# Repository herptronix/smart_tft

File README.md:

Smart TFT module
================

Open source (hardware & software) smart TFT module, based on:
 - Microchip PIC32MX795F512L microcontroller
 - 3.2" TFT 320x240, ILI9320/9325 controller
 - optional µSD card, for extra storage

This module has three operational modes:
 - slave: an other microcontroller sends commands to the TFT through UART (1M bauds, 8N1)
 - embedded app: the user includes its application directly into the PIC32
 - setup: setup menu, for touchscreen callibration, gamma adjustement & software demo; enter this mode by keeping the touchscreen pressed while powering on the 5V PSU.

Small video: https://www.youtube.com/watch?v=Nt97tPhJtdA
Some explanations (french only): http://herptronix.blogspot.fr/

## Pins & wirepads description ##

## Software modules ##

## Screenshots ##

## Pickit3 ##

Status
======

Maintained

 - 2014/03/31 Add sprite & font converters (sources & win32 exe)
 - 2014/02/27 Add display orientation support (limited to BSP) & Minor bug fixes
 - 2014/02/01 Minor bug fixes (p2d_font.c / touchCalib.c / gui_w_usr_entry.c)
 - 2014/01/15 Add a quick & dirty (... and not yet completed) dev. guide
 - 2014/01/09 Add a serial remote example
 - 2013/12/29 Rev. A (improved P2D/GUI, FAT-FS support, setup menu, serial comm support)
 - 2013/08/11 First GUI version (not on git)
 - 2013/07/13 First P2D version (not on git)

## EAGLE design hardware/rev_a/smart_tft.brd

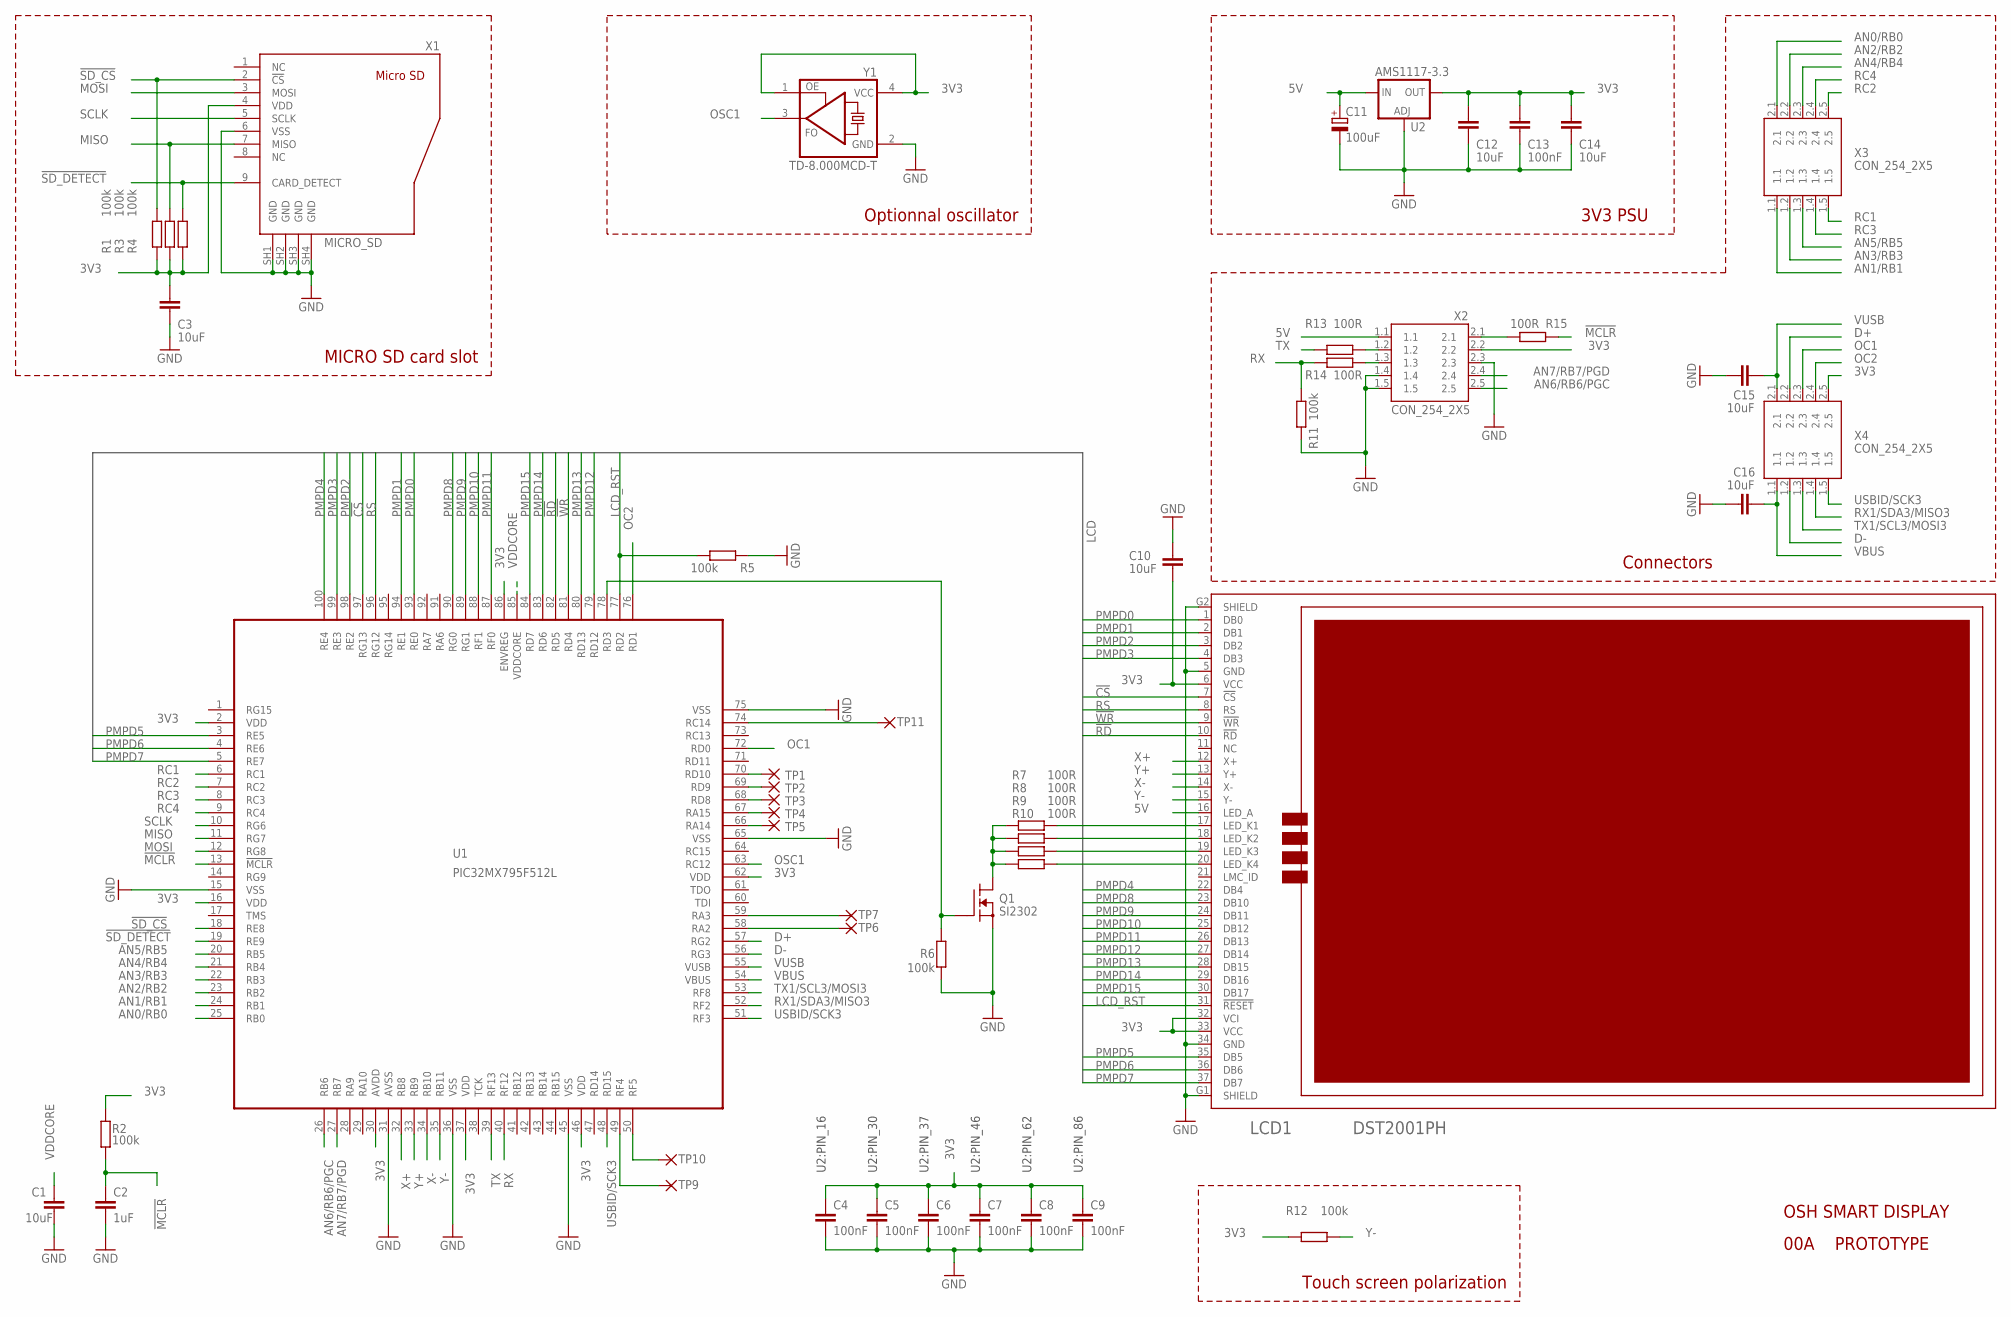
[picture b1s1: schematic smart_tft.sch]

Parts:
C1, C3, C10, C12, C14, C15, C16: 10uF; C0805
C2: 1uF; C0603
C4, C5, C6, C7, C8, C9, C13: 100nF; C0603
C11: 100uF; SMC_D
LCD1: DST2001PH
Q1: SI2302; SOT23-BEC
R1, R2, R3, R4, R5, R6, R11, R12: 100k; R0603
R7, R8, R9, R10, R13, R14, R15: 100R; R0603
TP1, TP2, TP3, TP4, TP5, TP6, TP7, TP9, TP10, TP11: 1.27R
U1: PIC32MX795F512L; TQFP100-14X14
U2: AMS1117-3.3; SOT223
X1: MICRO_SD; SD_MICRO
X2, X3, X4: CON_254_2X5; 2X5_CMS
Y1: TD-8.000MCD-T; ASF

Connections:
3V3: C3.1, C4.1, C5.1, C6.1, C7.1, C8.1, C9.1, C10.2, C12.1, C13.1, C14.1, LCD1.6 (VCC), LCD1.32 (VCI), LCD1.33 (VCC), R1.1, R2.2, R3.2, R4.2, R12.2, U1.2 (VDD), U1.16 (VDD), U1.30 (AVDD), U1.37 (VDD), U1.46 (VDD), U1.62 (VDD), U1.86 (ENVREG), U2.4 (OUT), X1.4 (VDD), X2.2.2, X4.2.5, Y1.1 (OE), Y1.4 (VCC)
5V: C11.+, LCD1.16 (LED_A), U2.3 (IN), X2.1.1
!CS: LCD1.7 (!CS), U1.97 (RG13)
!MCLR: C2.1, R2.1, R15.1, U1.13 (!MCLR)
!RD: LCD1.10 (!RD), U1.82 (RD5)
!SD_CS: R1.2, U1.18 (RE8), X1.2 (!CS)
!SD_DETECT: R4.1, U1.19 (RE9), X1.9 (CARD_DETECT)
!WR: LCD1.9 (!WR), U1.81 (RD4)
AN0/RB0: U1.25 (RB0), X3.2.1
AN1/RB1: U1.24 (RB1), X3.1.1
AN2/RB2: U1.23 (RB2), X3.2.2
AN3/RB3: U1.22 (RB3), X3.1.2
AN4/RB4: U1.21 (RB4), X3.2.3
AN5/RB5: U1.20 (RB5), X3.1.3
AN6/RB6/PGC: U1.26 (RB6), X2.2.5
AN7/RB7/PGD: U1.27 (RB7), X2.2.4
D+: U1.57 (RG2), X4.2.2
D-: U1.56 (RG3), X4.1.2
GND: C1.1, C2.2, C3.2, C4.2, C5.2, C6.2, C7.2, C8.2, C9.2, C10.1, C11.-, C12.2, C13.2, C14.2, C15.2, C16.2, LCD1.5 (GND), LCD1.34 (GND), LCD1.G1 (SHIELD), LCD1.G2 (SHIELD), Q1.E (S), R5.1, R6.1, R11.1, U1.15 (VSS), U1.31 (AVSS), U1.36 (VSS), U1.45 (VSS), U1.65 (VSS), U1.75 (VSS), U2.1 (ADJ), X1.6 (VSS), X1.SH1 (GND), X1.SH2 (GND), X1.SH3 (GND), X1.SH4 (GND), X2.1.4, X2.1.5, X2.2.3, Y1.2 (GND)
LCD_RST: LCD1.31 (!RESET), R5.2, U1.77 (RD2)
MISO: R3.1, U1.11 (RG7), X1.7 (MISO)
MOSI: U1.12 (RG8), X1.3 (MOSI)
unnamed: TP6.P$1, U1.58 (RA2)
unnamed: Q1.C (D), R7.1, R8.1, R9.1, R10.1
unnamed: Q1.B (G), R6.2, U1.78 (RD3)
unnamed: R13.2, X2.1.2
unnamed: R14.2, X2.1.3
unnamed: TP7.P$1, U1.59 (RA3)
unnamed: TP5.P$1, U1.66 (RA14)
unnamed: TP4.P$1, U1.67 (RA15)
unnamed: LCD1.20 (LED_K4), R10.2
unnamed: LCD1.19 (LED_K3), R9.2
unnamed: LCD1.18 (LED_K2), R8.2
unnamed: LCD1.17 (LED_K1), R7.2
unnamed: TP3.P$1, U1.68 (RD8)
unnamed: TP2.P$1, U1.69 (RD9)
unnamed: TP1.P$1, U1.70 (RD10)
unnamed: TP9.P$1, U1.49 (RF4)
unnamed: TP10.P$1, U1.50 (RF5)
unnamed: TP11.P$1, U1.74 (RC14)
unnamed: R15.2, X2.2.1
OC1: U1.72 (RD0), X4.2.3
OC2: U1.76 (RD1), X4.2.4
OSC1: U1.63 (RC12), Y1.3 (FO)
PMPD0: LCD1.1 (DB0), U1.93 (RE0)
PMPD1: LCD1.2 (DB1), U1.94 (RE1)
PMPD2: LCD1.3 (DB2), U1.98 (RE2)
PMPD3: LCD1.4 (DB3), U1.99 (RE3)
PMPD4: LCD1.22 (DB4), U1.100 (RE4)
PMPD5: LCD1.35 (DB5), U1.3 (RE5)
PMPD6: LCD1.36 (DB6), U1.4 (RE6)
PMPD7: LCD1.37 (DB7), U1.5 (RE7)
PMPD8: LCD1.23 (DB10), U1.90 (RG0)
PMPD9: LCD1.24 (DB11), U1.89 (RG1)
PMPD10: LCD1.25 (DB12), U1.88 (RF1)
PMPD11: LCD1.26 (DB13), U1.87 (RF0)
PMPD12: LCD1.27 (DB14), U1.79 (RD12)
PMPD13: LCD1.28 (DB15), U1.80 (RD13)
PMPD14: LCD1.29 (DB16), U1.83 (RD6)
PMPD15: LCD1.30 (DB17), U1.84 (RD7)
RC1: U1.6 (RC1), X3.1.5
RC2: U1.7 (RC2), X3.2.5
RC3: U1.8 (RC3), X3.1.4
RC4: U1.9 (RC4), X3.2.4
RS: LCD1.8 (RS), U1.96 (RG12)
RX: R11.2, R14.1, U1.40 (RF12)
RX1/SDA3/MISO3: U1.52 (RF2), X4.1.4
SCLK: U1.10 (RG6), X1.5 (SCLK)
TX: R13.1, U1.39 (RF13)
TX1/SCL3/MOSI3: U1.53 (RF8), X4.1.3
USBID/SCK3: U1.48 (RD15), U1.51 (RF3), X4.1.5
VBUS: C16.1, U1.54 (VBUS), X4.1.1
VDDCORE: C1.2, U1.85 (VDDCORE)
VUSB: C15.1, U1.55 (VUSB), X4.2.1
X+: LCD1.12 (X+), U1.32 (RB8)
X-: LCD1.14 (X-), U1.34 (RB10)
Y+: LCD1.13 (Y+), U1.33 (RB9)
Y-: LCD1.15 (Y-), R12.1, U1.35 (RB11)

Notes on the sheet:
PROTOTYPE
00A
U2:PIN_16
U2:PIN_37
U2:PIN_46
U2:PIN_62
U2:PIN_86
U2:PIN_30
Touch screen polarization
MICRO SD card slot
Optionnal oscillator
3V3 PSU
Connectors
OSH SMART DISPLAY

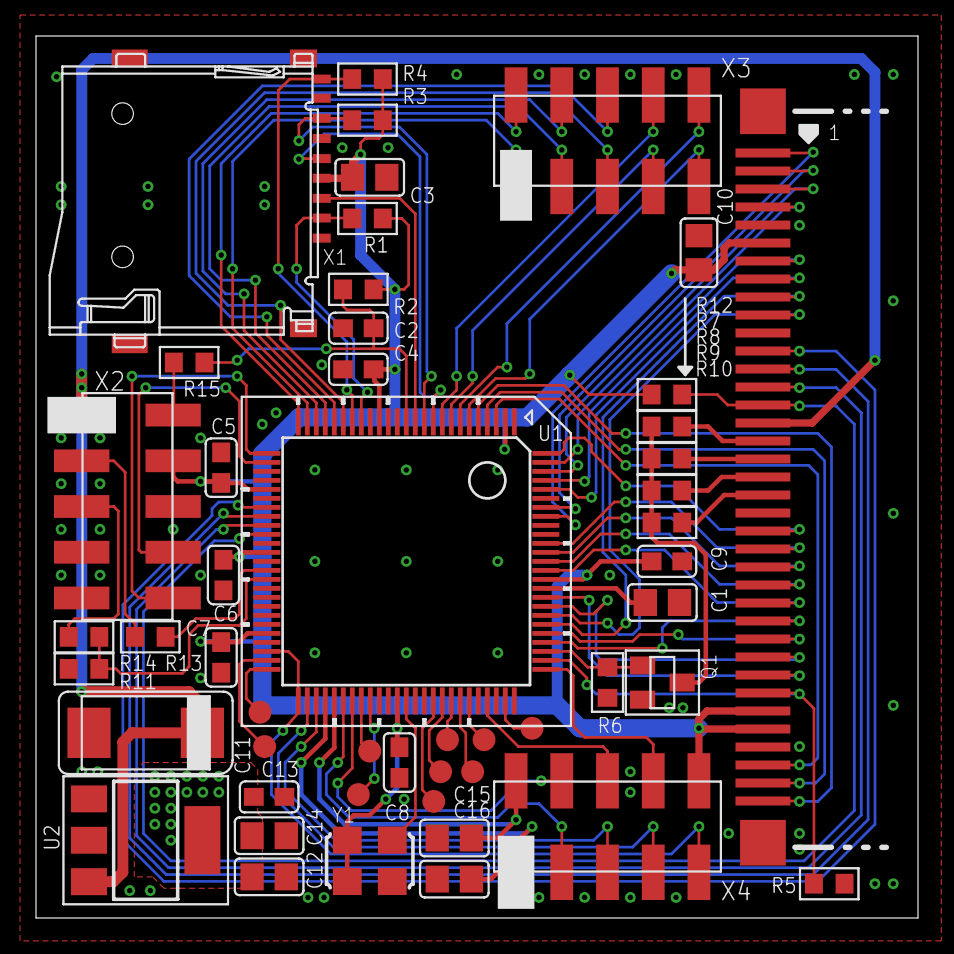
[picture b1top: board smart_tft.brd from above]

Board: 2 copper layers, 49.0 x 49.0 mm, 50 parts (0 on the bottom side), 78 nets.

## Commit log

2014-01-09 Add a serial remote example
2014-01-15 Add a quick & dirty dev. guide
2014-02-01 changed P2D.h to p2d.h
2014-02-01 Bug fixes
2014-02-27 Add display orientation support (limited to BSP) & Minor bug fixes
2014-03-31 Add sprite & font converters
